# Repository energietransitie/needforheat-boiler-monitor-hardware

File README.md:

# NeedForHeat Boiler Monitor hardware <!-- omit in toc -->

This repository contains the open hardware design files for the NeedForHeat Boiler Monitor hardware, which consists of PCB and 3D printable pipeclamps for:

* Boiler-BASE module for the on the back of an [M5Stack CoreInk](https://docs.m5stack.com/en/core/coreink) device;
* Thermostat Cable Splitter module, which is inserted by the subject in the signal path between boiler and thermostat;
* Two pipe clamps with temperature sensors that can be clipped on the supply and return pipes that carry hot water from the boiler to the radiators and returning from the radiators.

This integrated device can:
* monitor OpenTherm signals between boiler and thermostat, similar to the [Twomes OpenTherm monitor](https://github.com/energietransitie/twomes-opentherm-monitor-hardware);
* monitor on/off signals between boiler and thermostat that do not adhere to the OpenTherm standard;
* monitor with supply and return water temperatures, similar to the [Twomes Temperature Monitor Hardware](https://github.com/energietransitie/twomes-temp-monitor-hardware).

<!-- it would be better to have an image of the entire solution, including cables, like the assignment presentation -->

## Table of contents <!-- omit in toc -->
- [General info](#general-info)
- [Producing](#producing)
  - [Printed Circuit Board](#printed-circuit-board)
  - [Enclosures](#enclosures)
- [Deploying](#deploying)
  - [Cost](#cost)
  - [Connecting](#connecting)
  - [Disconnecting](#disconnecting)
- [Developing](#developing)
  - [Printed Circuit Board](#printed-circuit-board-1)
  - [Enclosures](#enclosures-1)
- [Features](#features)
- [Status](#status)
- [License](#license)
- [Citation](#citation)
- [Credits](#credits)

## General info
This repository contains the open hardware designs files and production files for the NeedForHeat Boiler Monitor. It also includes a `docs` folder with recent printouts of:
* BoilerBASE: [schematics](./docs/BoilerBase-sch.pdf) and [PCB layout](./docs/BoilerBase-pcb.pdf);
* Thermostat Cable Splitter:[schematics](./docs/ThermostatCableSplitter-sch.pdf) and [PCB layout](./docs/ThermostatCableSplitter-pcb.pdf);
* Pipe Clamps: [schematics](./docs/PipeClamp-pcb.pdf) and [PCB layout](./docs/PipeClamp-pcb.pdf).

The splitter features a 4 wire pluggable screw terminal on each side in which the cables can be connected to in almost any order.

The associated firmware that you need to run on this device was not yet implemented. I will be a combination of:
* [needforheat-generic-firmware](https://github.com/energietransitie/needforheat-generic-firmware) compiled with `env:M5STACK_COREINK`
* [twomes-opentherm-monitor-firmware](https://github.com/energietransitie/twomes-opentherm-monitor-firmware) 
* [twomes-boiler-base-firmware](https://github.com/energietransitie/twomes-boiler-base-firmware).

## Producing

### Printed Circuit Board
To manufacture the printed circuit board you can use various PCB services. 

The folder [pcb production](./pcb) includes all exported files needed to have the PCBs manufactured by [JLCPCB](https://www.jlcpcb.com). Upload a [zipped gerber file](./pcb/Gerber) to the [JLCPCB quote page](https://cart.jlcpcb.com/quote), select the amount of PCBs and a colour for the silkscreen. All other options can be left on default.

If you do not want to solder components on the PCB yourself, select `PCB assembly` and JLCPCB will do it for you (even for through-hole components if you so desire). This will take you to a page where the BOM and POS file can be uploaded. Use the files in [BOM-CPL](./pcb/BOM-CPL). 

JLCPCB provides detailed steps on their website to select component assembly, including wave soldering. For wave soldering or through-hole component assembly, specify this requirement when uploading your BOM and POS files. 

In the table below, you will find the files per PCB.

| PCB                       | zipped gerber                                                                                               | BOM                                                                                                                           | CPL                                                                                                   | Components that do not need to be placed |
| ------------------------- | ----------------------------------------------------------------------------------------------------------- | ----------------------------------------------------------------------------------------------------------------------------- | ----------------------------------------------------------------------------------------------------- | ---------------------------------------- |
| BoilerBASE                | [GERBER-BoilerBASE.zip](pcb\BoilerBASE\jlcpcb\GERBER-BoilerBASE.zip)                                        | [BOM-BoilerBASE.csv](pcb\BoilerBASE\jlcpcb\BoilerBASE\BOM-BoilerBASE.csv)                                                     | [BOM-BoilerBASE.csv](pcb\BoilerBASE\jlcpcb\BoilerBASE\CPL-BoilerBASE.csv)                             |                                          |
| Thermostat Cable Splitter | [GERBER-ThermostatCableSplitter.zip](pcb\ThermostatCableSplitter\jlcpcb\GERBER-ThermostatCableSplitter.zip) | [BOM-ThermostatCableSplitter.csv](pcb\ThermostatCableSplitter\jlcpcb\ThermostatCableSplitter\BOM-ThermostatCableSplitter.csv) | [CPL-ThermostatCableSplitter.csv](pcb\jlcpcb\ThermostatCableSplitter\CPL-ThermostatCableSplitter.csv) | `R13`, `R14`, `R15`                      |
| Pipe Clamps               | [GERBER-PipeClamp.zip](pcb\PipeClamp\jlcpcb\GERBER-PipeClamp.zip)                                           | [BOM-PipeClamp.csv](pcb\PipeClamp\jlcpcb\Splitter\BOM-PipeClamp.csv)                                                          | [CPL-PipeClamp.csv](pcb\jlcpcb\Splitter\CPL-PipeClamp.csv)                                            |                                          |

### Enclosures

To manufacure the pipe clamps you can use your own 3D printer or use a 3D printing service. 

The folder [enclosure](./enclosure) contains exported STL files for:
* [Boiler-BASE enclosure](./enclosure/BoilerBASE/fabrication/BoilerBase.STL);
* [Pipe Clamp enclosure](./enclosure/PipeClamp/fabrication/PipeClamp.stl) and [Pipe Clamp enclosure locks](./enclosure/PipeClamp/fabrication/PipeClamp_lock.stl). 
 
The STL files can be imported into any slicer and turned into G-Code for a 3D printer.

We do not yet have designs for the Thermostata Cable Splitter.

## Deploying

### Cost
To deploy the NeedForHeat Boiler Module to a home, you need all hardware listed below. Prices indicate price per Boiler Monitor, based on ordering enough hardware for 10 Boiler Monitors, June 2024 including 21% VAT and shipping to an address in the Netherlands.

| #   | Item                                                                                                                                                 | Supplier      | Price per Unit |   Subtotal |   Shipping |       Total |
| --- | ---------------------------------------------------------------------------------------------------------------------------------------------------- | ------------- | -------------: | ---------: | ---------: | ----------: |
| 1   | BoilerBASE PCB                                                                                                                                       |               |          €2.38 |      €2.38 |      €2.38 |       €4,79 |
| 1   | BoilerBASE Enclosure                                                                                                                                 | JLCPCB        |          €1.23 |      €1.23 |      €2.38 |       €3.60 |
| 1   | Thermostat Cable Splitter PCB[^1]                                                                                                                    | JLCPCB        |          €5.02 |      €5.02 |      €3.23 |       €8.25 |
| 1   | Thermostat Cable Splitter enclosure                                                                                                                  |               |          €2.38 |      €2.38 |      €2.38 |       €4,79 |
| 2   | [Pluggable Terminal Blocks (5.08 mm. 4 ways)](https://nl.farnell.com/camdenboss/ctb9209-4/terminal-block-pluggable-4pos/dp/2493644)                  |               |          €1.15 |      €2.30 |      €1.82 |       €3.12 |
| 2   | Pipe Clamp PCB                                                                                                                                       | JLCPCB        |          €3.41 |      €6.81 |      €2.30 |       €9.11 |
| 1   | Pipe Clamp enclosure                                                                                                                                 | JLCPCB        |          €1.00 |      €2.00 |      €2.38 |       €4.38 |
| 4   | [LEGO pen with friction](https://www.blokjeskoning.nl/product/pen-stroef-pen-stroef-zwart/)                                                          | Blokjeskoning |          €0.03 |      €0.12 |      €0.30 |       €0.42 |
| 1   | [M5Stack CoreInk](https://www.tinytronics.nl/nl/platformen-en-systemen/m5stack/e-paper/m5stack-m5core-ink-met-1.54-inch-e-paper-e-ink-display-esp32) | TinyTronics   |         €43.00 |     €43.00 |      €0.00 |      €43.00 |
| 2   | [RJ12 cable (male-male; 6P6C; straight; 1 m)](https://www.allekabels.nl/rj12-kabel/7400/1181351/telefoonkabel-rj12.html)                             | AlleKabels    |          €3.08 |      €6.16 |      €0.13 |       €6.29 |
| 1   | [RJ45 cable (male-male; 8P8C; straight; 1 m)](https://www.allekabels.nl/cat5e-kabel/15545/1098185/uutp-kabel-cat-5e.html)                            | AlleKabels    |          €1.29 |      €1.29 |      €0.13 |       €1.42 |
| 1   | [USB-A 230V charger + USB-A to USB-C cable](https://www.allekabels.nl/usb-oplader/4508/3636716/usb-a-oplader-usb-c-kabel.html)                       | AlleKabels    |         €14.95 |     €14.95 |      €0.13 |      €15.08 |
|     | **TOTAL**                                                                                                                                            |               |                | **€87.64** | **€17.46** | **€107.65** |

[^1]: Only the Thermostat Cable Splitter remains at the home of the user; the rest can be sent back after the measurement period.

### Connecting

Assuming that the PCBs are fully assembled, the devices have an enclosure, and the device has been programmed with the [needforheat-p1-reader-firmware](https://github.com/energietransitie/needforheat-p1-reader-firmware), you can proceed and connect the device as follows:

Tools needed;
- Screwdriver (flat head, 3 mm)
- Wire cutter
- Wire stripper

Steps:
1. **Unplug the power**
   - Unplug the boiler and thermostat from power outlets.

2. **Connect the Boiler Monitor**
   1. Cut the signal cable between the boiler and thermostat within 1.5 meters of a power outlet.
   2. Strip 2 cm of the outer sheath and 0.5 cm of insulation from each wire.
   3. Insert wires into the green pluggable screw terminal connectors and tighten screws.
   4. Attach connectors to the Thermostat Cable Splitter (boiler side: connector `J2` on the PCB and `CV` on the enclosure, thermostat side: connector `J1` on the PCB and  `T` on the enclosure).
   5. Connect the BoilerBASE to the M5Stack CoreInk MI-BUS using the 2x8 male pin header.
   6. Use an ethernet cable (RJ45) to connect the Thermostat Cable Splitter (connector `J3` on the PCB) to the BoilerBASE (connector `J3` on the PCB).
   7. Power the M5Coreink+BoilerBASE via USB-C.
   8. Insert PipeClamp PCBs into enclosures and secure with locking pins.
   9. Use cables (RJ12) to connect the BoilerBASE (connector `J1` and `J2` on the PCB; order does not matter) to the PipeClamps (connector `J1` on the PCB).
   10. Attach the M5Coreink+BoilerBASE to the boiler with its magnetic back on a flat metal surface of the boiler.
   11. Check LEDs on the Thermostat Cable Splitter; if not blinking, switch wires 1 & 2 or 3 & 4 in the pluggable screw connector on the thermostat side.

3. **Plug the power back in**
   - Reconnect the boiler and thermostat to power outlets.

### Disconnecting

After the measurement period, the user only needs to unplug the RJ45 cable from the Thermostat Cable Splitter, which can remain connected with the thermostat cable in the user's home. The rest can be sent back and re-used in other homes. 

## Developing

### Printed Circuit Board

To change the hardware design of the PCBs, you need:
* [KiCad version 8.0.0 or later](https://www.kicad.org/download/) installed to change te PCB design. 

The KiCad source files of the PCB can be found in subfolders of the folder [pcb](./pcb):
* [BoilerBASE](./pcb/BoilerBASE/)
* [ThermostatCableSplitter](./pcb/ThermostatCableSplitter/)
* [PipeClamp](./pcb/PipeClamp/)

To convert the PCBs into a format suitable for fabrication, consult the webpage of your PCB manufacturer of choice. For example, see the [JLCPCB guide on how to export Gerbers](https://support.jlcpcb.com/article/149-how-to-generate-gerber-and-drill-files-in-kicad) and the  [JLCPCB guide how to export the BOM and POS files](https://support.jlcpcb.com/article/84-how-to-generate-the-bom-and-centroid-file-from-kicad). You may also use a KiCad plug-in for this purpose such as [kicad-jlcpcb-tools](https://github.com/Bouni/kicad-jlcpcb-tools).

### Enclosures
To change the hardware design of an enclosure, you need either:
* [Autodesk Fusion 360]([https://www.kicad.org/download/](https://www.autodesk.com/products/fusion-360/personal)) installed (Autodesk provides 30 day free trials and [free one-year educational access](https://www.autodesk.com/education/edu-software/overview?sorting=featured&filters=individual) to its products and services for eligible students, teachers and research staff); 
* or [FreeCAD](https://www.freecadweb.org/), an open source alternative.

The source files of the enclosures can be found in subfolders of the folder [enclosure](./enclosure):
* [BoilerBASE](./enclosure/BoilerBASE)
* ThermostatCableSplitter (*We do not yet have a design for this enclosure*)
* [PipeClamp](./enclosure/PipeClamp/)

## Features
The  NeedForHeat Boiler Monitor features the follwoing main hardware components:
- [x] Thermostat Cable Splitter PCB with 4-wire pluggable screw terminals and circuit to monitor OpenTherm communication, including LEDs and optocouplers;
- [x] Circuit in the Thermostat Cable Splitter that allows (mostly) order agnostic connection of the 4 wires per pluggable screw connector (see also [connecting the devices](#connecting-the-devices));
- [x] Pipe Clamp PCB to measure temperatures from the supply and return pipes below the boiler.
- [x] Pipe Clamp enclosures, which can be 3D printed as a clamp that presses the temperature sensors agains a water pipe below a heating boiler and provide a  locking mechanism the prevent the PCB from falling out.

To-do:
- Thermostat Cable Splitter
  - [ ] Reconsider the choice of pluggable screw connectors: reversible? lever-operated (e.g., [WAGO PCB terminal block](https://www.wago.com/global/c/pcb-terminal-blocks-and-pluggable-connectors?f=%3Afacet_product_Produkttyp_7845%3APCB%20terminal%20blocks%3Afacet_product_Leiterplattenklemmentyp_10295%3APCB%20terminal%20blocks%3Afacet_product_Polzahl_6%3A4%3Afacet_product_Betaetigungsart_01_3901%3ALever&sort=relevance&page=1&pageSize=50))?
  - [ ] Redesign the thermostat side such that the user can mount the wires truly in any order.
  - [ ] Design an enclosure.
* BoilerBASE
  - [ ] Add an 868 MHz SMD transceiver chip to enable monitoring of wireless thermostats.
  - [ ] Add connectors to BOM and CPL files and repair rotation errors to enable through-hole soldering by JLCPC.
  - [ ] Evaluate relocating the 2x8 pin header from the bottom side to the top side of the PCB to reduce JLCPCB manufacturing costs. 
  - [ ] Improve BOM and CPL for JLCPCB through hole assembly. 
  - [ ] Design an enclosure that adds multiple mounting options
    - [ ] room to embed permanent magnets to make it stick to flat metallic surfaces of boilers;
    - [ ] a tie wrap hole.
* Pipe Clamps
  - [ ] Redesign 3D printed enclosures to ensure strength and durability.

## Status
Project is:  _in_progress_

## License
The hardware designs in this repository are available under the [CERN-OHL-P v2 license](./LICENSE), Copyright 2024 [Research group Energy Transition, Windesheim University of Applied Sciences](https://windesheim.nl/energietransitie)

## Citation

If you use this repository in your research or work, please cite the following pre-print, which describes the overall NeedForHeat DataGear system of which this repository is a part:

> Ter Hofte, H., & van Ravenzwaaij, N. (2025). *NeedForHeat DataGear: An Open Monitoring System to Accelerate the Residential Heating Transition*. arXiv preprint arXiv:2509.06927. https://doi.org/10.48550/arXiv.2509.06927

**Note:** This is a pre-print submitted on 8 Sep 2025 and has not yet been peer-reviewed. For the full paper, see [https://arxiv.org/abs/2509.06927](https://arxiv.org/abs/2509.06927).

## Credits
This hardware is a collaborative effort of:
* Bram Busch · [@BlueRisen](https://github.com/BlueRisen)
* Daan Tellegen · [@D-Tellegen](https://github.com/D-Tellegen)

Earlier versions of this open hardware were designed by:
* Huub Buter · [@h-buter](https://github.com/h-buter>)
* Mirjam van Wee
* Kees Fokker
  
Product owners:
* Henri ter Hofte · [@henriterhofte](https://github.com/henriterhofte)
* Marco Winkelman · [@MarcoW71](https://github.com/MarcoW71)

We use and gratefully acknowlegde the efforts of the makers of the following designs:

* [Twomes OpenTherm monitor](https://github.com/energietransitie/twomes-opentherm-monitor-hardware), by Research group Energy Transition at Windesheim University of Applied Sciences, licenced under [Apache 2.0](https://raw.githubusercontent.com/energietransitie/twomes-opentherm-monitor-hardware/main/LICENSE)
* [Twomes Temperature Monitor Hardware](https://github.com/energietransitie/twomes-temp-monitor-hardware), by Research group Energy Transition at Windesheim University of Applied Sciences, licenced under [Apache 2.0](https://raw.githubusercontent.com/energietransitie/twomes-temp-monitor-hardware/main/LICENSE)
* [KiCad Libraries](https://kicad.github.io/), by the KiCad Development Team, licensed under [an adapted version of the CC-BY-SA 4.0 License](https://www.kicad.org/libraries/license/)

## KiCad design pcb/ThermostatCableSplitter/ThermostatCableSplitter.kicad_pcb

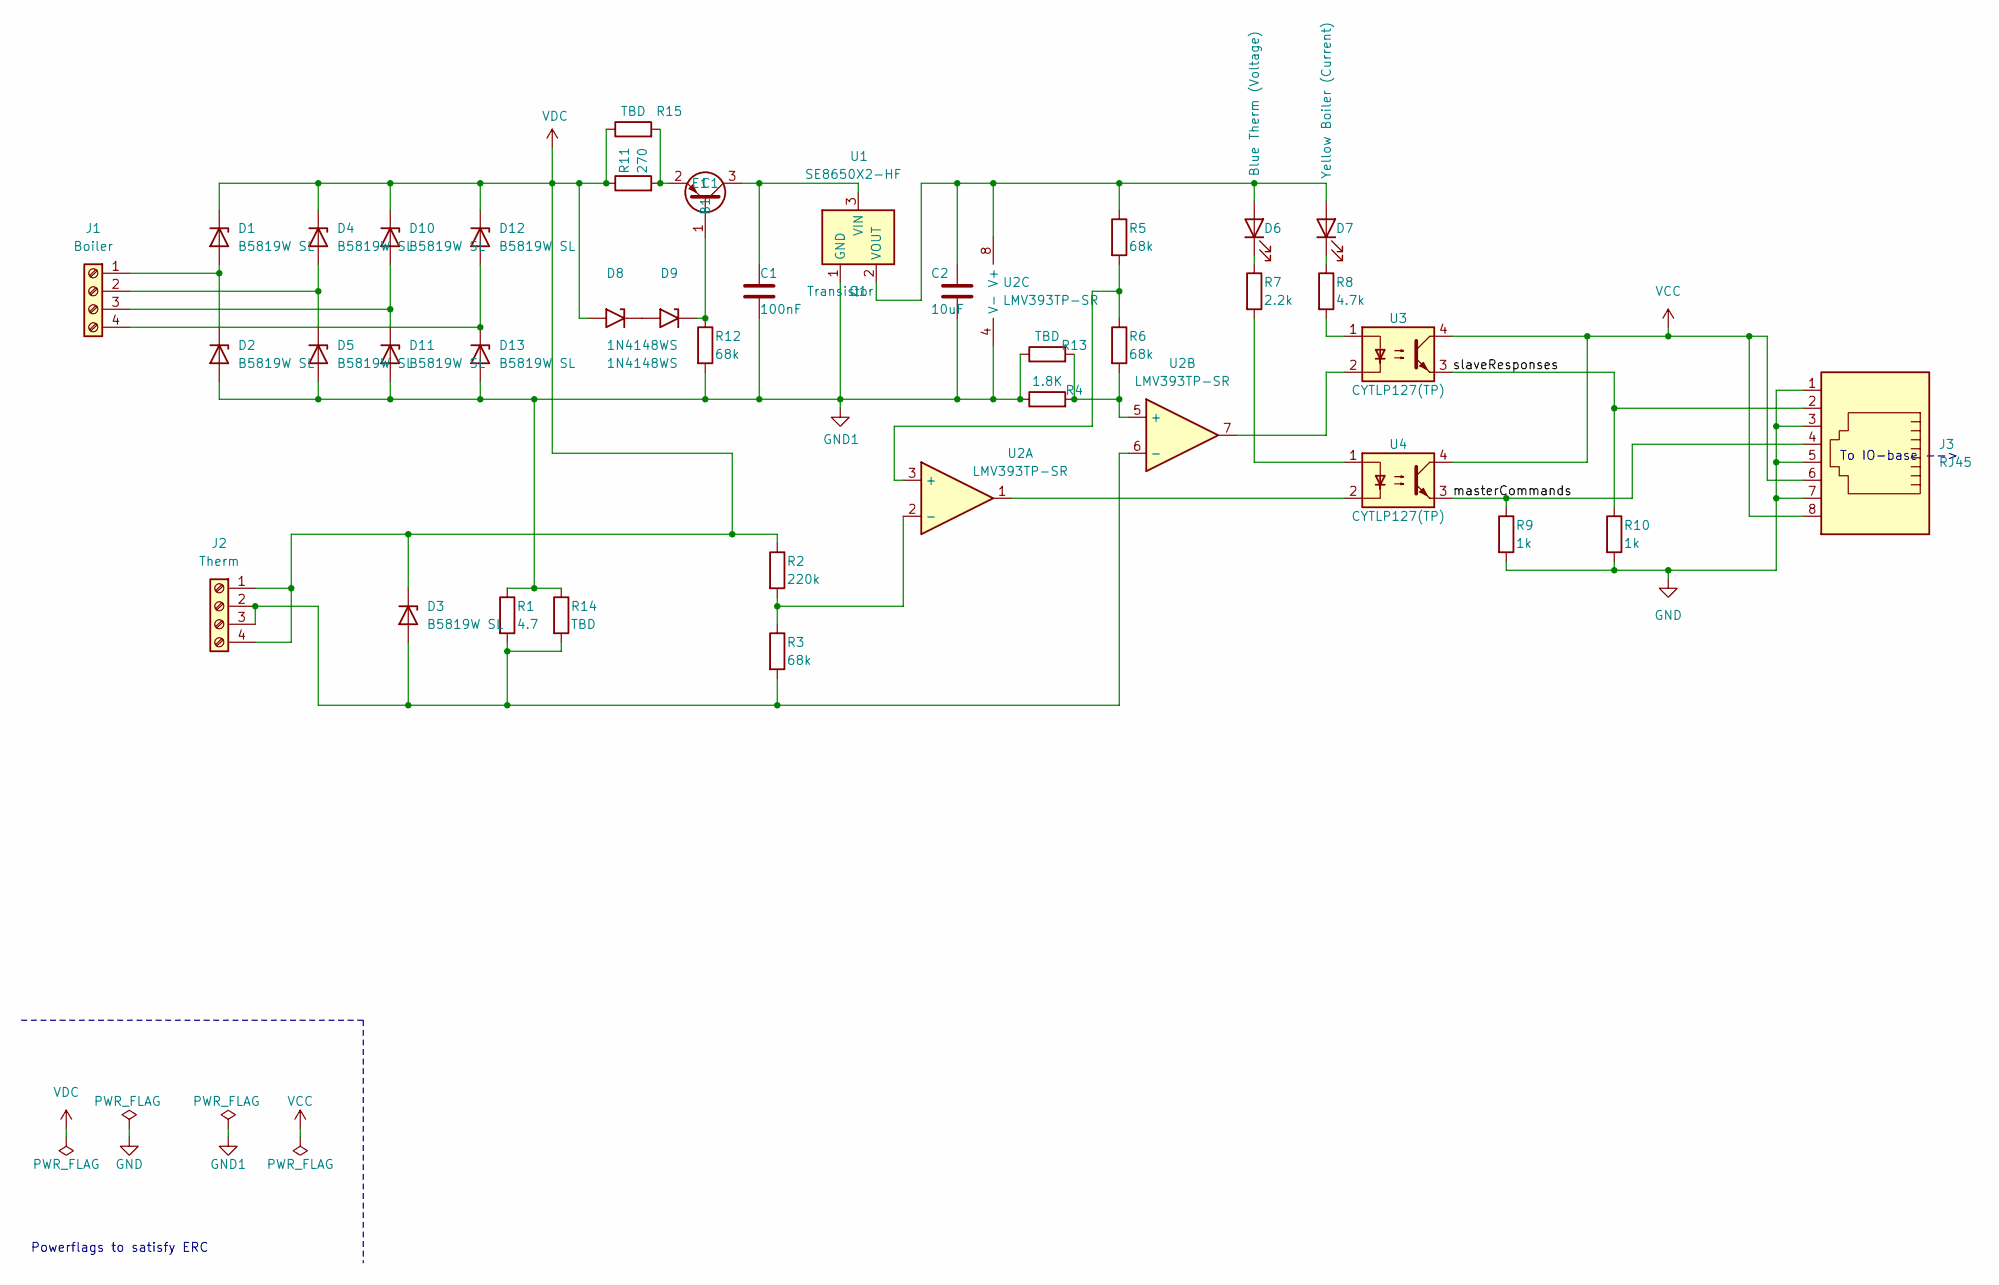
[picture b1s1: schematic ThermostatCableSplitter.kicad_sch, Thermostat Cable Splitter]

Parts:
C1: 100nF; C_0805_2012Metric
C2: 10uF; C_0805_2012Metric
D1, D2, D3, D4, D5, D10, D11, D12, D13: B5819W SL; D_SOD-123; LCSC C8598
D6: Blue Therm (Voltage); LED_0603_1608Metric
D7: Yellow Boiler (Current); LED_0603_1608Metric
D8, D9: 1N4148WS; D_SOD-323_HandSoldering; LCSC C2128
J1: Boiler; PhoenixContact_MSTBA_2,5_4-G-5,08_1x04_P5.08mm_Horizontal
J2: Therm; PhoenixContact_MSTBA_2,5_4-G-5,08_1x04_P5.08mm_Horizontal
J3: RJ45; RJ45_Amphenol_54602-x08_Horizontal; Mouser SS90000001
Q1: Transistor; SOT-23; LCSC C2149
R1: 4.7; R_0603_1608Metric
R2: 220k; R_0603_1608Metric
R3, R5, R6, R12: 68k; R_0603_1608Metric
R4: 1.8K; R_0603_1608Metric
R7: 2.2k; R_0603_1608Metric
R8: 4.7k; R_0603_1608Metric
R9, R10: 1k; R_0603_1608Metric
R11: 270; R_0603_1608Metric
R13, R14, R15: TBD; R_0805_2012Metric_Pad1.20x1.40mm_HandSolder
U1: SE8650X2-HF; SOT-23; LCSC C496615
U2: LMV393TP-SR; SOIC-8_3.9x4.9mm_P1.27mm; LCSC C97672
U3, U4: CYTLP127(TP); SO-4_4.4x3.6mm_P2.54mm; LCSC C2836429

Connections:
/masterCommands: J3.4, R9.1, U4.3
/slaveResponses: J3.2, R10.1, U3.3
GND: J3.1, J3.3, J3.5, J3.7, R9.2, R10.2
GND1: C1.2, C2.2, D2.2 (A), D5.2 (A), D11.2 (A), D13.2 (A), R1.1, R4.1, R12.2, R13.1, R14.1, U1.1 (GND), U2.4 (V-)
unnamed: D1.2 (A), D2.1 (K), J1.1
unnamed: D3.2 (A), J2.2, J2.3, R1.2, R3.2, R14.2, U2.6 (-)
unnamed: D4.2 (A), D5.1 (K), J1.2
unnamed: C2.1, D6.2 (A), D7.2 (A), R5.1, U1.2 (VOUT), U2.8 (V+)
unnamed: D6.1 (K), R7.1
unnamed: D7.1 (K), R8.1
unnamed: D8.1 (A1), D9.2 (A2)
unnamed: D9.1 (A1), Q1.1 (B1), R12.1
unnamed: D10.2 (A), D11.1 (K), J1.3
unnamed: D12.2 (A), D13.1 (K), J1.4
unnamed: C1.1, Q1.3 (C1), U1.3 (VIN)
unnamed: Q1.2 (E1), R11.2, R15.2
unnamed: R7.2, U4.1
unnamed: R8.2, U3.1
unnamed: U2.1, U4.2
unnamed: U2.7, U3.2
unnamed: R5.2, R6.1, U2.3 (+)
unnamed: R2.2, R3.1, U2.2 (-)
unnamed: R4.2, R6.2, R13.2, U2.5 (+)
VCC: J3.6, J3.8, U3.4, U4.4
VDC: D1.1 (K), D3.1 (K), D4.1 (K), D8.2 (A2), D10.1 (K), D12.1 (K), J2.1, J2.4, R2.1, R11.1, R15.1

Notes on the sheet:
Powerflags to satisfy ERC
To IO-base -->

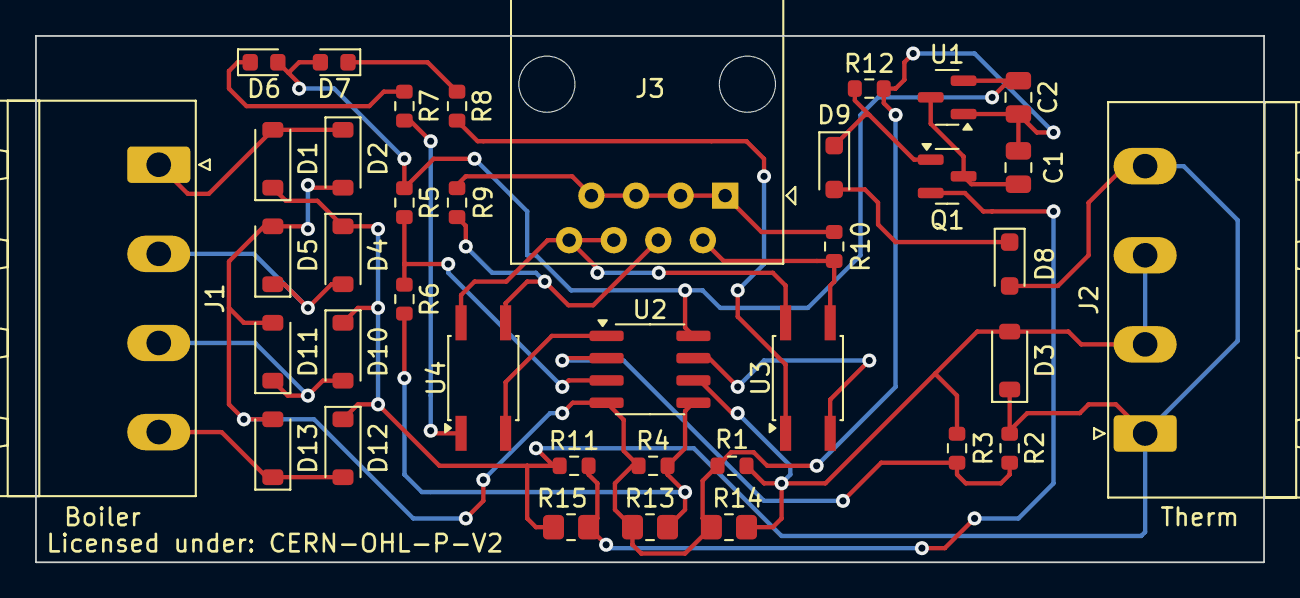
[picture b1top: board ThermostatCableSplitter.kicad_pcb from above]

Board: 2 copper layers, 70.0 x 30.0 mm, 38 parts (0 on the bottom side), 25 nets.

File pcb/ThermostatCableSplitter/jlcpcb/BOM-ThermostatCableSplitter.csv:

Comment,Designator,Footprint,LCSC
10uF,C2,C_0805_2012Metric,C15850
1k,"R10,R9",R_0603_1608Metric,C21190
1N4148WS,"D8,D9",D_SOD-323_HandSoldering,C2128
Transistor,Q1,SOT-23,C2149
220k,R2,R_0603_1608Metric,C22961
270,R11,R_0603_1608Metric,C22966
4.7k,R8,R_0603_1608Metric,C23162
4.7,R1,R_0603_1608Metric,C23164
68k,"R12,R3,R5,R6",R_0603_1608Metric,C23231
100nF,C1,C_0805_2012Metric,C28233
CYTLP127(TP),"U3,U4",SO-4_4.4x3.6mm_P2.54mm,C2836429
Blue Therm (Voltage),D6,LED_0603_1608Metric,C2986058
1.8K,R4,R_0603_1608Metric,C4177
2.2k,R7,R_0603_1608Metric,C4190
SE8650X2-HF ,U1,SOT-23,C496615
Yellow Boiler (Current),D7,LED_0603_1608Metric,C72038
Boiler,"J1,J2","PhoenixContact_MSTBA_2,5_4-G-5,08_1x04_P5.08mm_Horizontal",C8446
B5819W SL,"D1,D10,D11,D12,D13,D2,D3,D4,D5",D_SOD-123,C8598
RJ45,J3,RJ45_Amphenol_54602-x08_Horizontal,C86577
LMV393TP-SR,U2,SOIC-8_3.9x4.9mm_P1.27mm,C97672
TBD,R14,R_0805_2012Metric_Pad1.20x1.40mm_HandSolder,
TBD,R15,R_0805_2012Metric_Pad1.20x1.40mm_HandSolder,
TBD,R13,R_0805_2012Metric_Pad1.20x1.40mm_HandSolder,

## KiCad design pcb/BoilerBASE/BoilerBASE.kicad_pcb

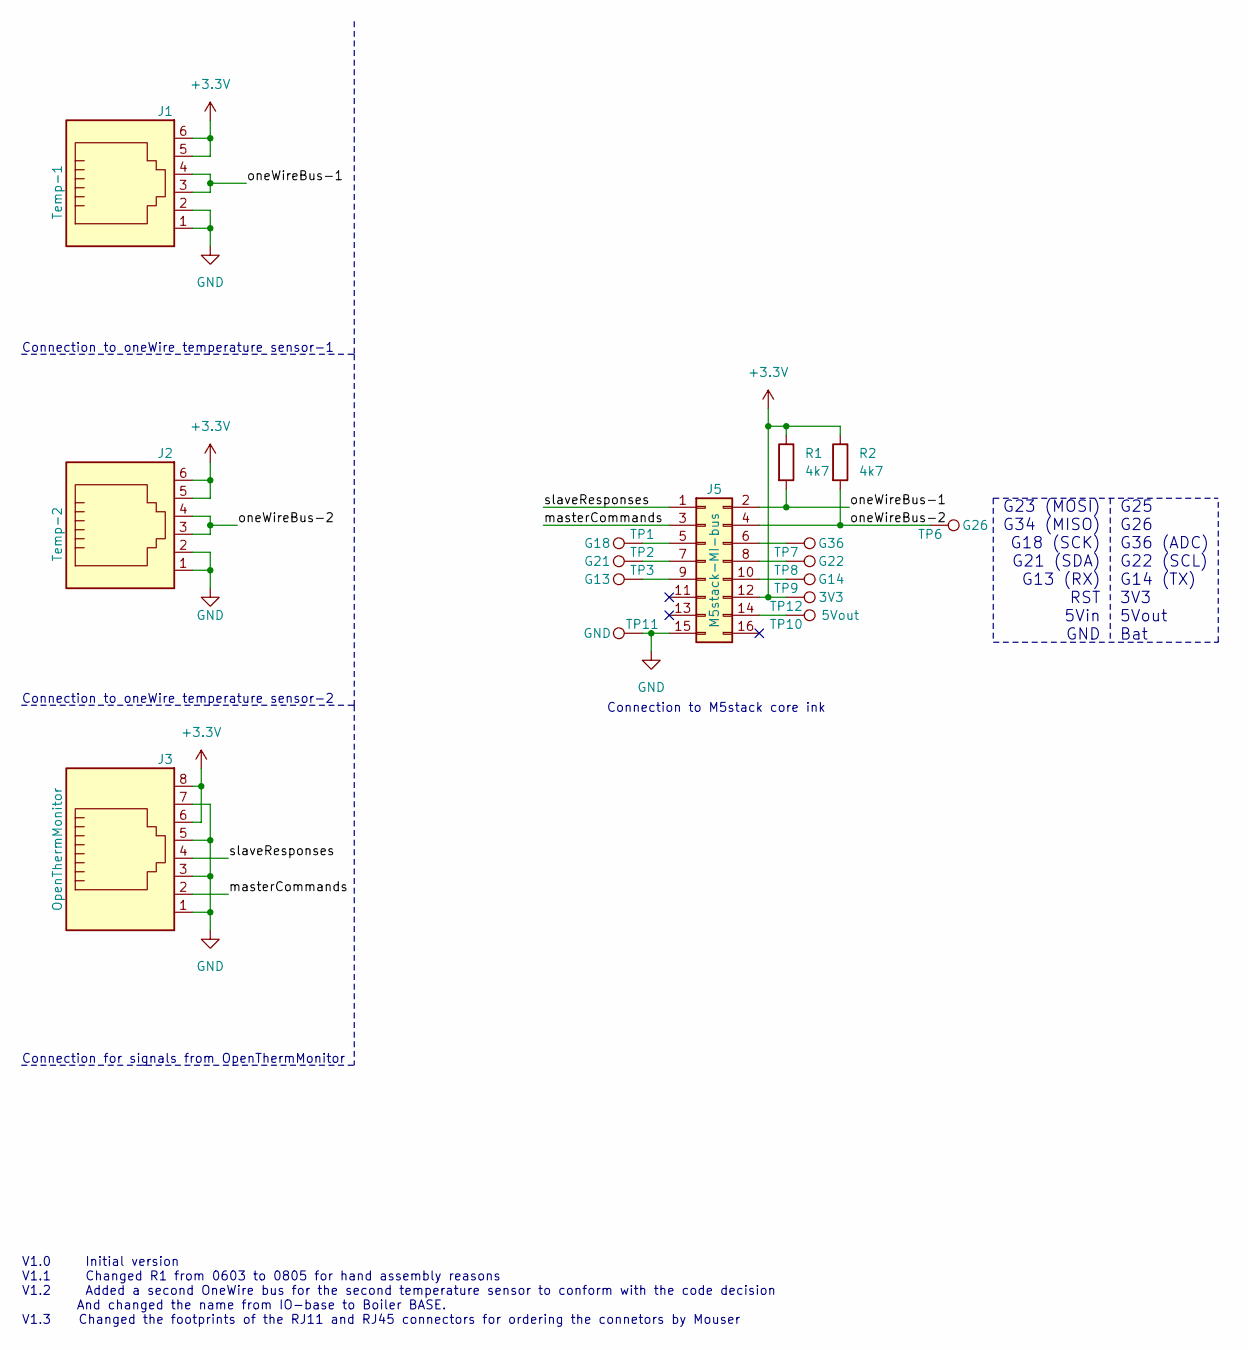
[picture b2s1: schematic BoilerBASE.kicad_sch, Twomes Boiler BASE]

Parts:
J1: Temp-1; RJ11 Stewart SS90000003
J2: Temp-2; RJ11 Stewart SS90000003
J3: OpenThermMonitor; RJ45 Stewart SS90000001
J5: M5stack-MI-bus; PinHeader_2x08_P2.54mm_Vertical
R1, R2: 4k7; R_0805_2012Metric_Pad1.20x1.40mm_HandSolder
TP1: G18; TestPoint_Pad_3.0x3.0mm
TP2: G21; TestPoint_Pad_3.0x3.0mm
TP3: G13; TestPoint_Pad_3.0x3.0mm
TP6: G26; TestPoint_Pad_3.0x3.0mm
TP7: G36; TestPoint_Pad_3.0x3.0mm
TP8: G22; TestPoint_Pad_3.0x3.0mm
TP9: G14; TestPoint_Pad_3.0x3.0mm
TP10: 5Vout; TestPoint_Pad_3.0x3.0mm
TP11: GND; TestPoint_Pad_3.0x3.0mm
TP12: 3V3; TestPoint_Pad_3.0x3.0mm

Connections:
+3.3V: J1.5, J1.6, J2.5, J2.6, J3.6, J3.8, J5.12, R1.1, R2.1, TP12.1
/masterCommands: J3.2, J5.3
/oneWireBus-1: J1.3, J1.4, J5.2, R1.2
/oneWireBus-2: J2.3, J2.4, J5.4, R2.2, TP6.1
/slaveResponses: J3.4, J5.1
GND: J1.1, J1.2, J2.1, J2.2, J3.1, J3.3, J3.5, J3.7, J5.15, TP11.1
unnamed: J5.5, TP1.1
unnamed: J5.6, TP7.1
unnamed: J5.7, TP2.1
unnamed: J5.8, TP8.1
unnamed: J5.9, TP3.1
unnamed: J5.10, TP9.1
unnamed: J5.14, TP10.1

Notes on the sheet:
Connection to M5stack core ink
G25 G26 G36 (ADC) G22 (SCL) G14 (TX) 3V3 5Vout Bat
Connection for signals from OpenThermMonitor
G23 (MOSI) G34 (MISO) G18 (SCK) G21 (SDA) G13 (RX) RST 5Vin GND
V1.0 Initial version V1.1 Changed R1 from 0603 to 0805 for hand assembly reasons V1.2 Added a second OneWire bus for the second temperature sensor to conform with the code decision And changed the name from IO-base to Boiler BASE. V1.3 Changed the footprints of the RJ11 and RJ45 connectors for orde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
Connection to oneWire temperature sensor-2
Connection to oneWire temperature sensor-1

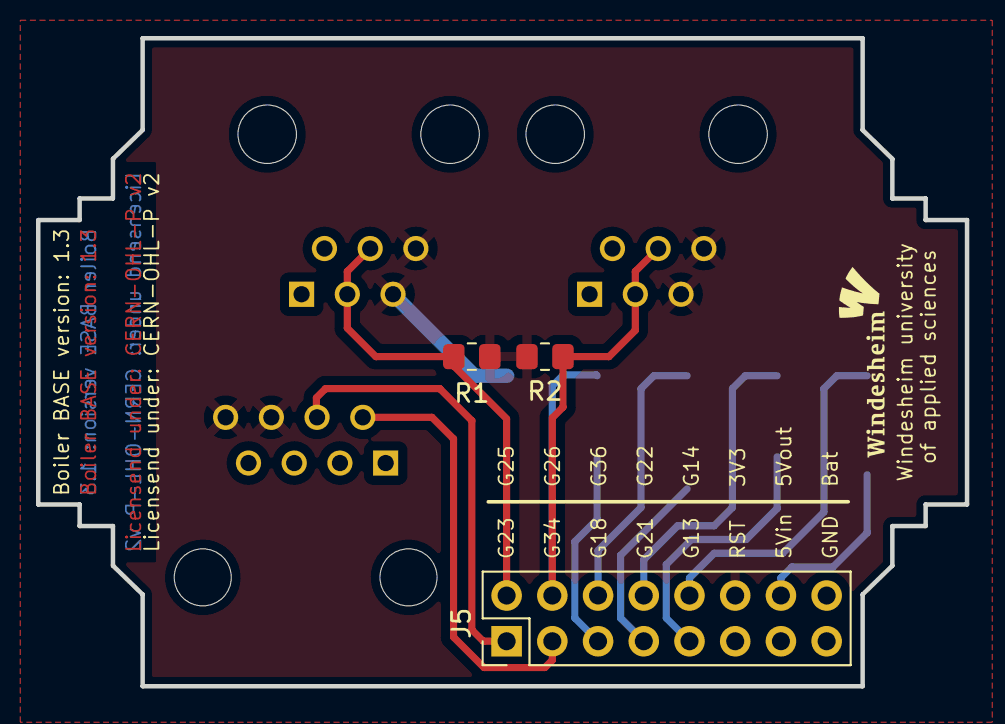
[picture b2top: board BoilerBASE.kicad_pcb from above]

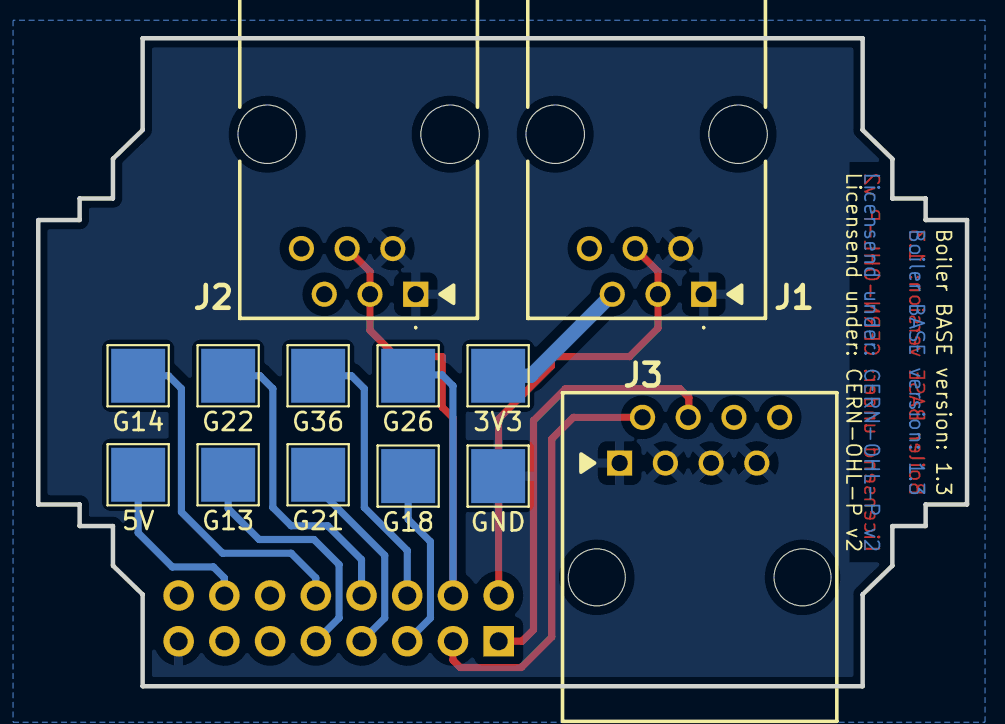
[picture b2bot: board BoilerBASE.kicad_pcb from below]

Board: 2 copper layers, 51.6 x 36.0 mm, 16 parts (13 on the bottom side), 13 nets.

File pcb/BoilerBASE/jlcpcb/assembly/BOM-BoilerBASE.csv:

Designator,Footprint,Quantity,Value,LCSC Part #
J1,RJ11,1,Temp-1,
J2,RJ11,1,Temp-2,
J3,RJ45-TE-connectivity,1,OpenThermMonitor,
J5,PinHeader_2x08_P2.54mm_Vertical,1,M5stack-MI-bus,
"R1, R2",R_0805_2012Metric_Pad1.20x1.40mm_HandSolder,2,4k7,

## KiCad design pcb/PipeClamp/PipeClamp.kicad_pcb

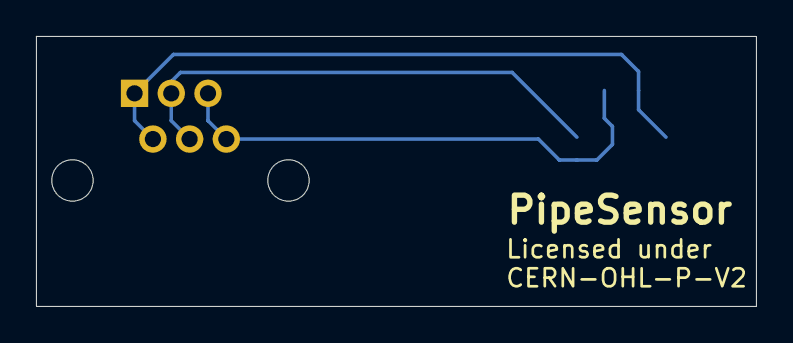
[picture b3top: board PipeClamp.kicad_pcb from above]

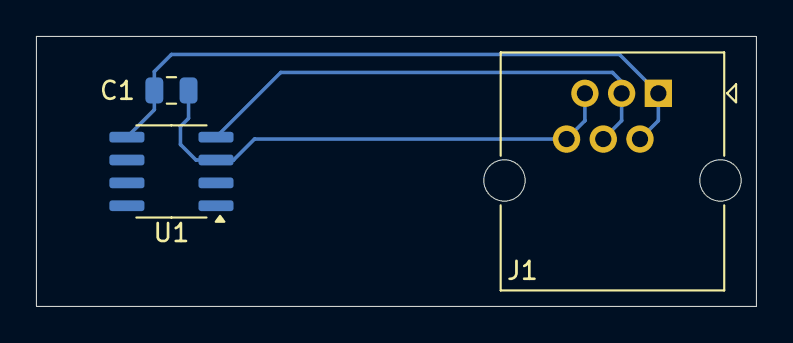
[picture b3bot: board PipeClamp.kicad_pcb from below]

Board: 2 copper layers, 40.0 x 15.0 mm, 3 parts (3 on the bottom side), 3 nets.

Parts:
C1: 100nF; C_0805_2012Metric
J1: RJ12; RJ25_Wayconn_MJEA-660X1_Horizontal
U1: DS18B20Z; SOIC-8_3.9x4.9mm_P1.27mm

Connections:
/GND-U1: C1.2, J1.1, J1.2, U1.5 (GND)
/VCC-U1: C1.1, J1.5, J1.6, U1.3 (V_{DD})
unnamed: J1.3, J1.4, U1.4 (DQ)

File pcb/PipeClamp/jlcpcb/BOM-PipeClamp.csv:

Comment,Designator,Footprint,LCSC
100nF,C1,C_0805_2012Metric,C49678
DS18B20Z,U1,SOIC-8_3.9x4.9mm_P1.27mm,C695837
RJ12,J1,RJ25_Wayconn_MJEA-660X1_Horizontal,C77859

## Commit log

2023-01-19 Boiler Base intial commit: schematic, pcb, enclosure, bom, gerbers
2023-01-20 added the schematics, pcb, enclosure, bom and gerbers of the OpenThermSplitter
2024-03-08 Update in anticipation of BoilerModule v1.0 design
2024-04-19 Create LICENSE
2024-06-19 New foto's for 4 cable splitter
2024-06-19 Schematics and PCBS commit to docs
2024-06-19 Create docs
2024-06-19 Create Temp
2024-06-19 PCB and Schematics
2024-06-19 Whole projects files
2024-06-19 Create test
2024-06-19 STL files for pipeclamps
2024-06-19 Create palceholder
2024-06-19 Create Placeholder
2024-06-19 STL bestanden
2024-06-19 Rename palceholder to Placeholder
2024-06-19 obj files
2024-06-19 JPG Files added
2024-06-19 Create polaceholder
2024-06-19 added back
2024-06-19 Update polaceholder
2024-06-19 Gerber file added
2024-06-19 BOM CPL files added
2024-06-19 Name change
2024-06-19 Added file
2024-06-24 aligned README and repo structure with other (future) hardware repos
2024-06-24 found old BoilerBASE sources again and added them, together with credits
2024-06-24 BoilerBASE improvements
2024-06-26 reorganized jlcpcb file locations and updated cost estimate
2024-06-27 gitignore *.lck files
2024-06-27 update to to for BoilerBASE BOM and CPL
2025-08-28 update PCB photos
2025-08-28 smaller pcb photos
2025-08-28 larger pcb photos, side by side
2025-08-28 add lock to enclosure photos

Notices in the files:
README.md:
The hardware designs in this repository are available under the [CERN-OHL-P v2 license](./LICENSE), Copyright 2024 [Research group Energy Transition, Windesheim University of Applied Sciences](https://windesheim.nl/energietransitie)
If you use this repository in your research or work, please cite the following pre-print, which describes the overall NeedForHeat DataGear system of which this repository is a part: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
pcb/BoilerBASE/BoilerBASE.kicad_pcb:
Licensend under: CERN-OHL-P v2
pcb/PipeClamp/PipeClamp.kicad_pcb:
Licensed under
CERN-OHL-P-V2
